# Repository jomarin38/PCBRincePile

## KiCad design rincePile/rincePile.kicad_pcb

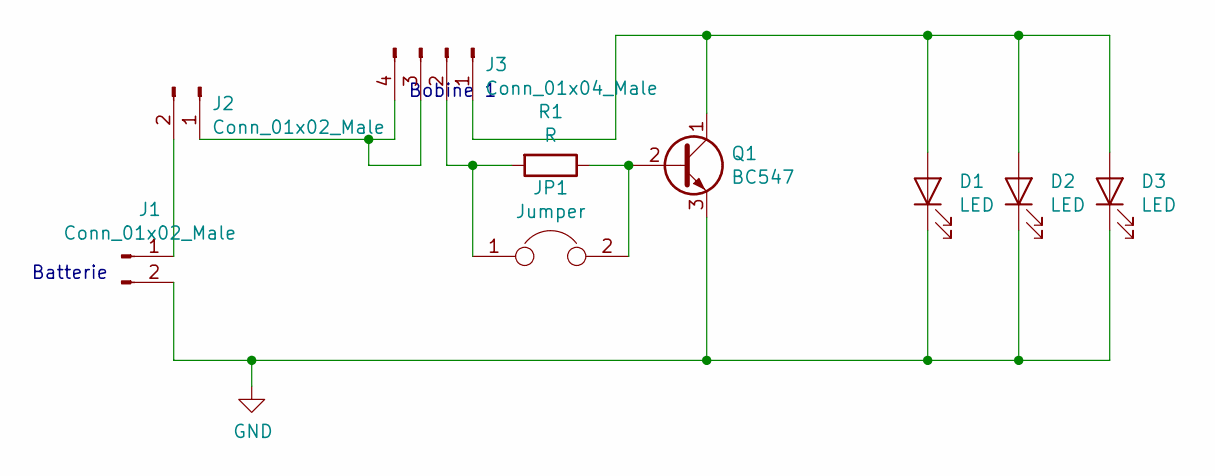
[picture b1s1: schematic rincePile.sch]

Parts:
D1, D2, D3: LED; LED_D5.0mm
J1, J2: Conn_01x02_Male; PinHeader_1x02_P2.54mm_Vertical
J3: Conn_01x04_Male; PinHeader_2x02_P2.54mm_Vertical
JP1: Jumper; SolderJumper-2_P1.3mm_Open_Pad1.0x1.5mm
Q1: BC547; TO-92_Inline
R1: R; R_Axial_DIN0207_L6.3mm_D2.5mm_P10.16mm_Horizontal

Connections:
GND: D1.1 (K), D2.1 (K), D3.1 (K), J1.2, Q1.3 (E)
unnamed: D1.2 (A), D2.2 (A), D3.2 (A), J3.1, Q1.1 (C)
unnamed: J1.1, J2.2
unnamed: J2.1, J3.3, J3.4
unnamed: J3.2, JP1.1, R1.2
unnamed: JP1.2, Q1.2 (B), R1.1

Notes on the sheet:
Batterie
Bobine 1

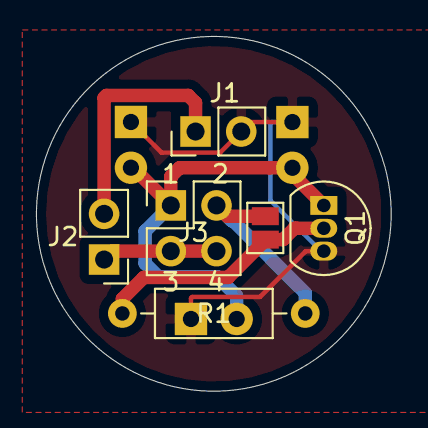
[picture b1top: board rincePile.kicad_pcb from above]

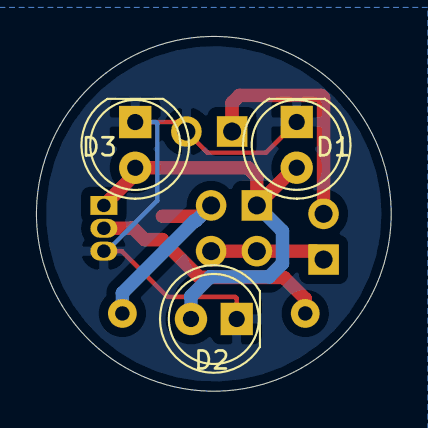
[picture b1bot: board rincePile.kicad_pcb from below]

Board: 2 copper layers, 19.7 x 19.7 mm, 9 parts (3 on the bottom side), 6 nets.

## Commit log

2022-04-02 initial version
2022-04-02 update PCB creation des gerber et fichiers de percage
2022-04-03 Adding solder masks
2022-04-03 Updating gerber settngs in pcb file
